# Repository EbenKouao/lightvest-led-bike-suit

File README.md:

# LightVest

LightVest is an open-source Bike Vest designed to be wearable technology. The product is a Bike Suit designed to increase a cyclist’s visibility, especially during the night. As well as improving cyclist communication and intent with other motorists and pedestrians.

## About this project:

This Bike Safety Product is designed to be open source. Feel free to contribute to make LightVest more robust. LightVest is designed for you to build on top of. Certain aspects of LightVest can be improved. Feel free to contribute, and explore more use cases.

Originally a video idea, aiming to build and launch a start-up in 4 weeks. You can find more information on the process on [smartbuilds.io](https://smartbuilds.io).
Alternatively, you can watch the full start up journey on my YouTube channel for context [Eben Kouao - The 4 Week Start-Up - Mini Documentary](https://www.youtube.com/channel/UCGxwyXJWEarxh2XWqvygiIg).

For more information visit: [lightvest.io](https://lightvest.io)

## Features

- A lightweight Weatherproof LED Vest (with IP67 Rated LEDs)
- Turn Signal’s – Fully programmable RGB LEDs
- Wireless remote to control the lights (with 4 fully customisable buttons)
- A Bike mount to attach to your Bike
- ON/OFF Switch Button
- Go Hand’s Free with an Inbuilt accelerometer – control Turn signals by from your bike handle
- Smart Mode – Send Data and track your Journey by Phone

## LightVest - Resources

This repo contains includes:

- Arduino Code
  - LightVest Remote
  - LightVest Wearable
- Breadboard Schematics (CAD and Fritzing)
  - LightVest Remote
  - LightVest Wearable
- PCB Schematics
  - LightVest Remote
  - LightVest Wearable
- 3D Prints
  - Remote
    - Breadboard Design:
      - Top Case
      - Bottom Case
      - Button (Arrow Keys)
    - PCB Design
      - Top Case
      - Bottom Case
      - Button (Circular)
  - Vest Case
  - L Connector Case

## Functionality of LightVest

| LED Strip            | Colour    | Function                |
| -------------------- | --------- | ----------------------- |
| Diamond Strip - Half | Yellow    | Turn Left or Right      |
| Diamond              | Strip Red | Red Abrupt Break Lights |
| Front Shoulder strip | Yellow    | Turn Left or Right      |
| All LED on Blinking  | Yellow    | Hazard / Emergency      |

## Requirement

Arduino Nano x 2
MPU6050 (Accelerometer)
LED Strip (WS2812B)
Jumper Wires
2 x Bluetooth HC-05

See the full Part List on LightVest's components on [smartbuilds.io](https://smartbuilds.io)

## Diagrams

### LightVest

### Remote

Support my [Future Projects on Patreon](https://www.patreon.com/ebenkouao)

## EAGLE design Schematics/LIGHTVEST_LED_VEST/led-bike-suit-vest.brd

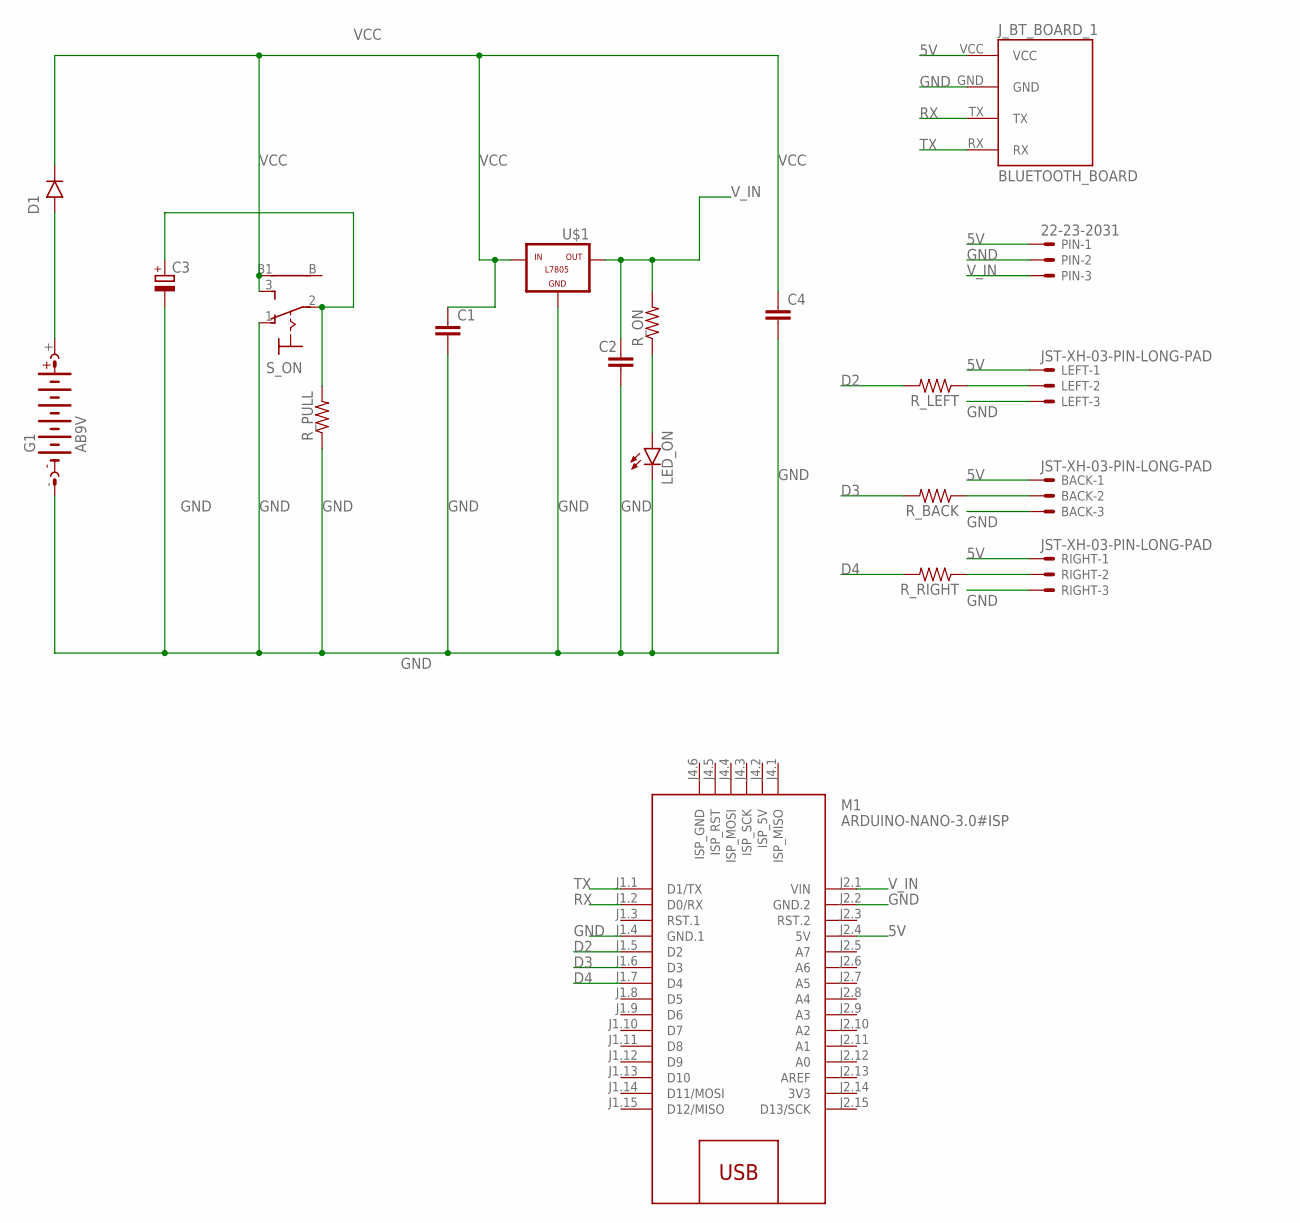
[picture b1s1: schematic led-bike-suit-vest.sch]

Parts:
BACK: JST-XH-03-PIN-LONG-PAD; JST-XH-03-PACKAGE-LONG-PAD
C1, C2, C4: C2.5/4; C2.5-4
C3: RCL_CPOL-EUE3.5-8; ELECTROLYTIC_CAP_RCL_E3,5-8
D1: 1N4001; DO41-10
G1: AB9V
J_BT_BOARD_1: BLUETOOTH_BOARD; BT_BOARD_FOOTPRINT
LED_ON: LED5MM
LEFT: JST-XH-03-PIN-LONG-PAD; JST-XH-03-PACKAGE-LONG-PAD
M1: ARDUINO-NANO-3.0#ISP
PIN: 22-23-2031
RIGHT: JST-XH-03-PIN-LONG-PAD; JST-XH-03-PACKAGE-LONG-PAD
R_BACK: PASSIVES_RESISTORPTH-1/4W; SPARKFUN-PASSIVES_AXIAL-0.4
R_LEFT: PASSIVES_RESISTORPTH-1/4W; SPARKFUN-PASSIVES_AXIAL-0.4
R_ON: PASSIVES_RESISTORPTH-1/4W; SPARKFUN-PASSIVES_AXIAL-0.4
R_PULL: PASSIVES_RESISTORPTH-1/4W; SPARKFUN-PASSIVES_AXIAL-0.4
R_RIGHT: PASSIVES_RESISTORPTH-1/4W; SPARKFUN-PASSIVES_AXIAL-0.4
S_ON: 9070-1W
U$1: -L7805; L7805

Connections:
3V3: M1.J2.14 (3V3)
5V: BACK.1, J_BT_BOARD_1.VCC, LEFT.1, M1.J2.4 (5V), PIN.1, RIGHT.1
D2: M1.J1.5 (D2), R_LEFT.P$2 (2)
D3: M1.J1.6 (D3), R_BACK.P$2 (2)
D4: M1.J1.7 (D4), R_RIGHT.P$2 (2)
GND: BACK.3, C1.2, C2.2, C3.-, C4.2, G1.-, J_BT_BOARD_1.GND, LED_ON.K (CATHODE), LEFT.3, M1.J1.4 (GND.1), M1.J2.2 (GND.2), PIN.2, RIGHT.3, R_PULL.P$1 (1), S_ON.1 (O), U$1.GND
unnamed: BACK.2, R_BACK.P$1 (1)
unnamed: LEFT.2, R_LEFT.P$1 (1)
unnamed: RIGHT.2, R_RIGHT.P$1 (1)
unnamed: C3.+, R_PULL.P$2 (2), S_ON.2
unnamed: D1.A (ANODE), G1.+
unnamed: LED_ON.A (ANODE), R_ON.P$1 (1)
RX: J_BT_BOARD_1.TX, M1.J1.2 (D0/RX)
TX: J_BT_BOARD_1.RX, M1.J1.1 (D1/TX)
VCC: C1.1, C4.1, D1.C (CATHODE), S_ON.3 (S), S_ON.B1, U$1.IN
V_IN: C2.1, M1.J2.1 (VIN), PIN.3, R_ON.P$2 (2), U$1.OUT

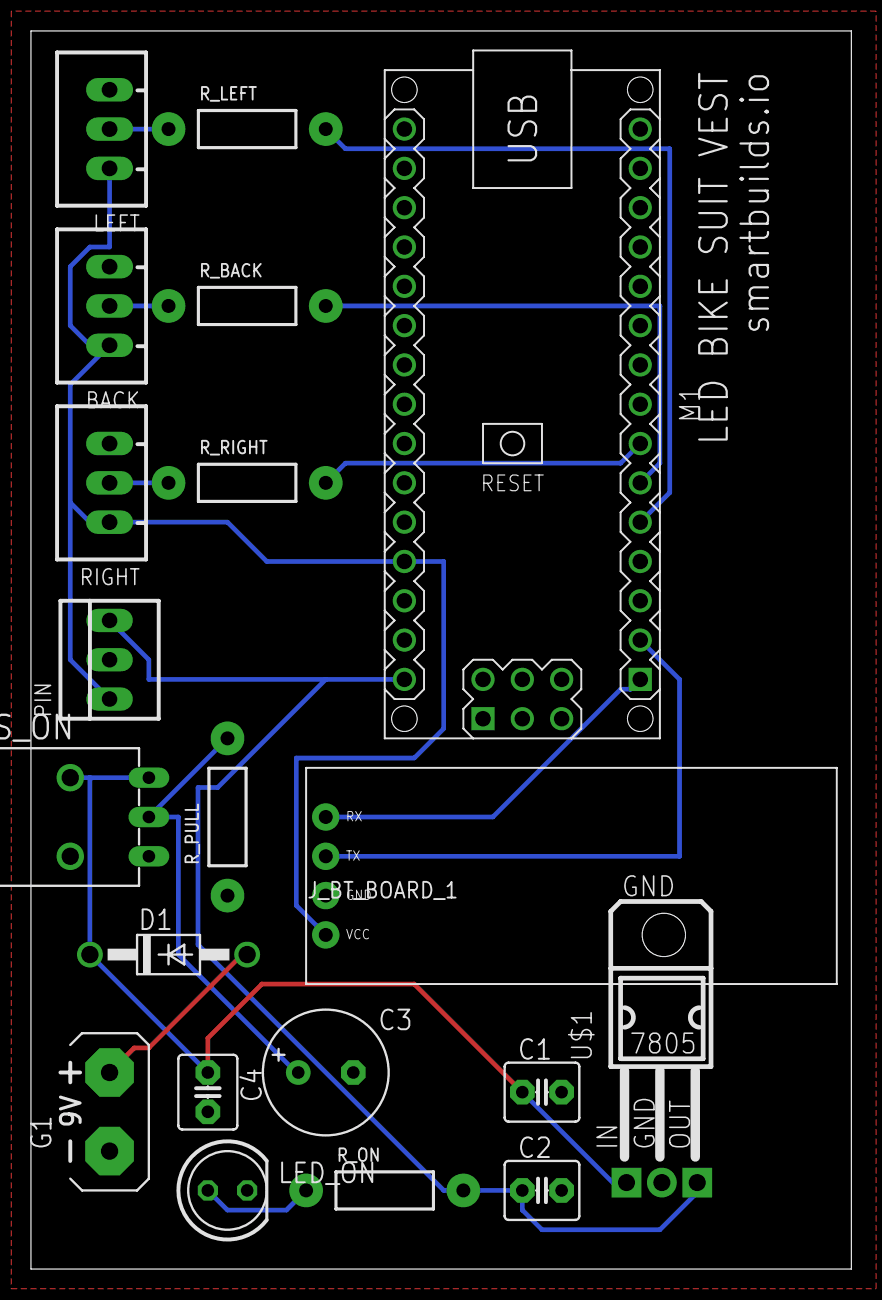
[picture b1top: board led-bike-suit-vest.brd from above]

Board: 2 copper layers, 53.0 x 80.0 mm, 20 parts (0 on the bottom side), 15 nets.

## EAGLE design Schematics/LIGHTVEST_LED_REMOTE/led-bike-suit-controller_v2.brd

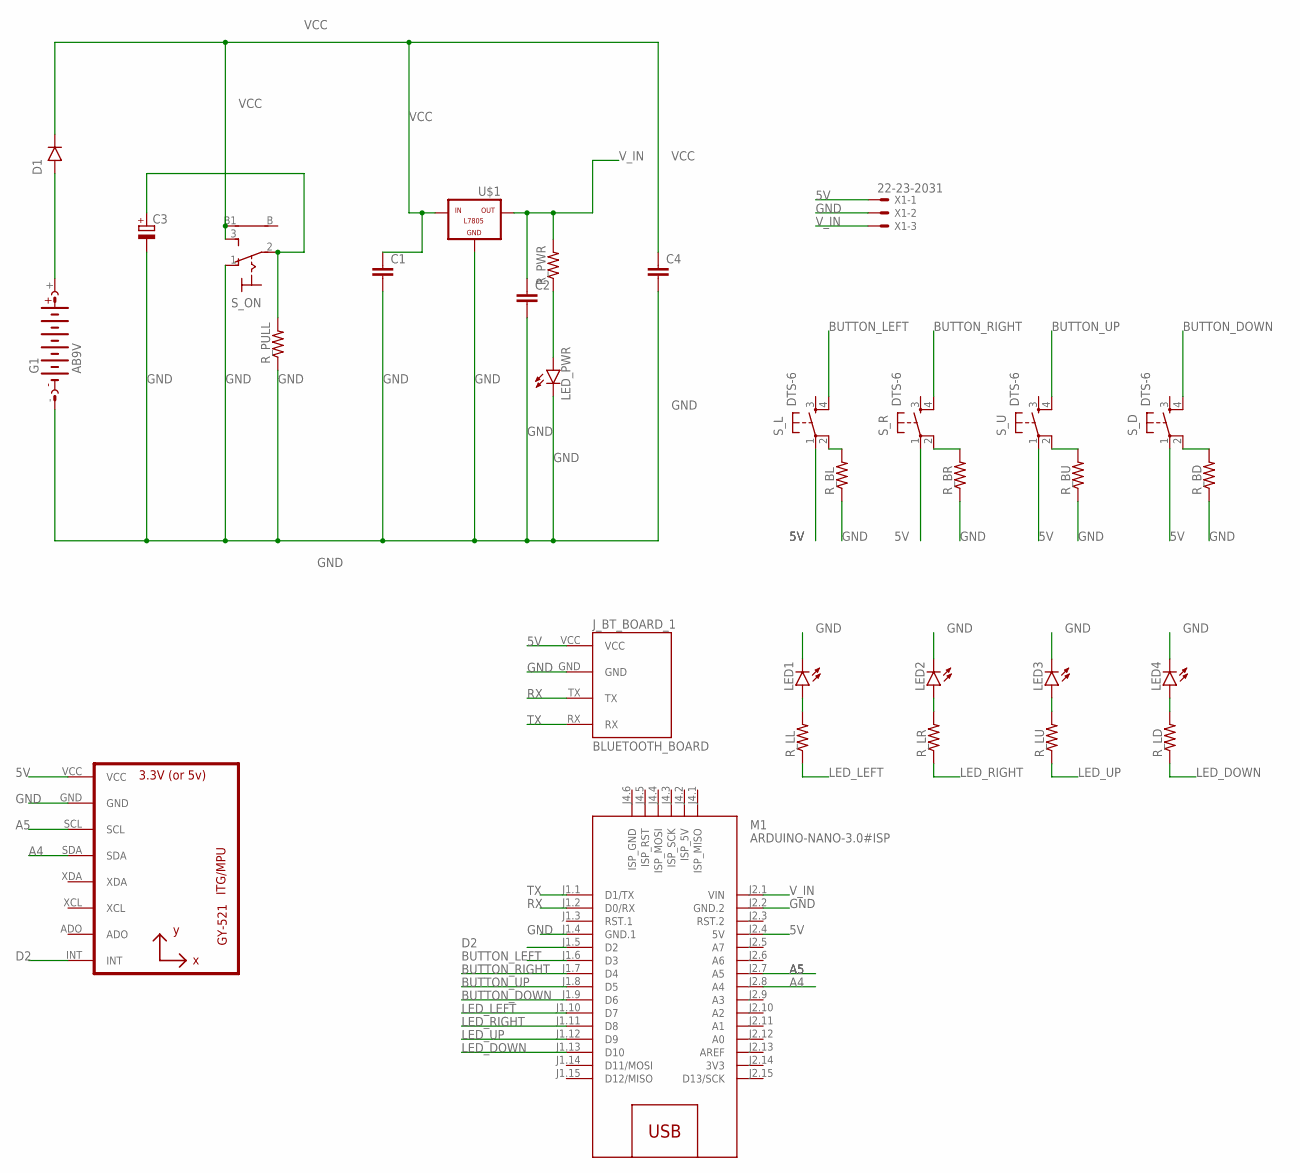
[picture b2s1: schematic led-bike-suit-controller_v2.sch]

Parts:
C1, C2, C4: C2.5/4; C2.5-4
C3: RCL_CPOL-EUE3.5-8; ELECTROLYTIC_CAP_RCL_E3,5-8
D1: 1N4001; DO41-10
G1: AB9V
J_BT_BOARD_1: BLUETOOTH_BOARD; BT_BOARD_FOOTPRINT
LED1, LED2, LED3, LED4: LED5MM; SPARKFUN-LED_LED5MM
LED_PWR: LED5MM
M1: ARDUINO-NANO-3.0#ISP
R_BD: PASSIVES_RESISTORPTH-1/4W; SPARKFUN-PASSIVES_AXIAL-0.4
R_BL: PASSIVES_RESISTORPTH-1/4W; SPARKFUN-PASSIVES_AXIAL-0.4
R_BR: PASSIVES_RESISTORPTH-1/4W; SPARKFUN-PASSIVES_AXIAL-0.4
R_BU: PASSIVES_RESISTORPTH-1/4W; SPARKFUN-PASSIVES_AXIAL-0.4
R_LD: PASSIVES_RESISTORPTH-1/4W; SPARKFUN-PASSIVES_AXIAL-0.4
R_LL: PASSIVES_RESISTORPTH-1/4W; SPARKFUN-PASSIVES_AXIAL-0.4
R_LR: PASSIVES_RESISTORPTH-1/4W; SPARKFUN-PASSIVES_AXIAL-0.4
R_LU: PASSIVES_RESISTORPTH-1/4W; SPARKFUN-PASSIVES_AXIAL-0.4
R_PULL: PASSIVES_RESISTORPTH-1/4W; SPARKFUN-PASSIVES_AXIAL-0.4
R_PWR: PASSIVES_RESISTORPTH-1/4W; SPARKFUN-PASSIVES_AXIAL-0.4
S_D: DTS-6
S_L: DTS-6
S_ON: 9070-1W
S_R: DTS-6
S_U: DTS-6
U1: GY-521MPU6050; GY-521
U$1: -L7805; L7805
X1: 22-23-2031

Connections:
3V3: M1.J2.14 (3V3)
5V: J_BT_BOARD_1.VCC, M1.J2.4 (5V), S_D.1, S_L.1, S_R.1, S_U.1, U1.VCC, X1.1
A4: M1.J2.8 (A4), U1.SDA
A5: M1.J2.7 (A5), U1.SCL
BUTTON_DOWN: M1.J1.9 (D6), S_D.4
BUTTON_LEFT: M1.J1.6 (D3), S_L.4
BUTTON_RIGHT: M1.J1.7 (D4), S_R.4
BUTTON_UP: M1.J1.8 (D5), S_U.4
D2: M1.J1.5 (D2), U1.INT
GND: C1.2, C2.2, C3.-, C4.2, G1.-, J_BT_BOARD_1.GND, LED1.K (C), LED2.K (C), LED3.K (C), LED4.K (C), LED_PWR.K (CATHODE), M1.J1.4 (GND.1), M1.J2.2 (GND.2), R_BD.P$1 (1), R_BL.P$1 (1), R_BR.P$1 (1), R_BU.P$1 (1), R_PULL.P$1 (1), S_ON.1 (O), U1.GND, U$1.GND, X1.2
LED_DOWN: M1.J1.13 (D10), R_LD.P$1 (1)
LED_LEFT: M1.J1.10 (D7), R_LL.P$1 (1)
LED_RIGHT: M1.J1.11 (D8), R_LR.P$1 (1)
LED_UP: M1.J1.12 (D9), R_LU.P$1 (1)
unnamed: LED1.A, R_LL.P$2 (2)
unnamed: R_BU.P$2 (2), S_U.2
unnamed: R_BD.P$2 (2), S_D.2
unnamed: LED2.A, R_LR.P$2 (2)
unnamed: R_BL.P$2 (2), S_L.2
unnamed: R_BR.P$2 (2), S_R.2
unnamed: LED3.A, R_LU.P$2 (2)
unnamed: LED4.A, R_LD.P$2 (2)
unnamed: C3.+, R_PULL.P$2 (2), S_ON.2
unnamed: D1.A (ANODE), G1.+
unnamed: LED_PWR.A (ANODE), R_PWR.P$1 (1)
RX: J_BT_BOARD_1.TX, M1.J1.2 (D0/RX)
TX: J_BT_BOARD_1.RX, M1.J1.1 (D1/TX)
VCC: C1.1, C4.1, D1.C (CATHODE), S_ON.3 (S), S_ON.B1, U$1.IN
V_IN: C2.1, M1.J2.1 (VIN), R_PWR.P$2 (2), U$1.OUT, X1.3

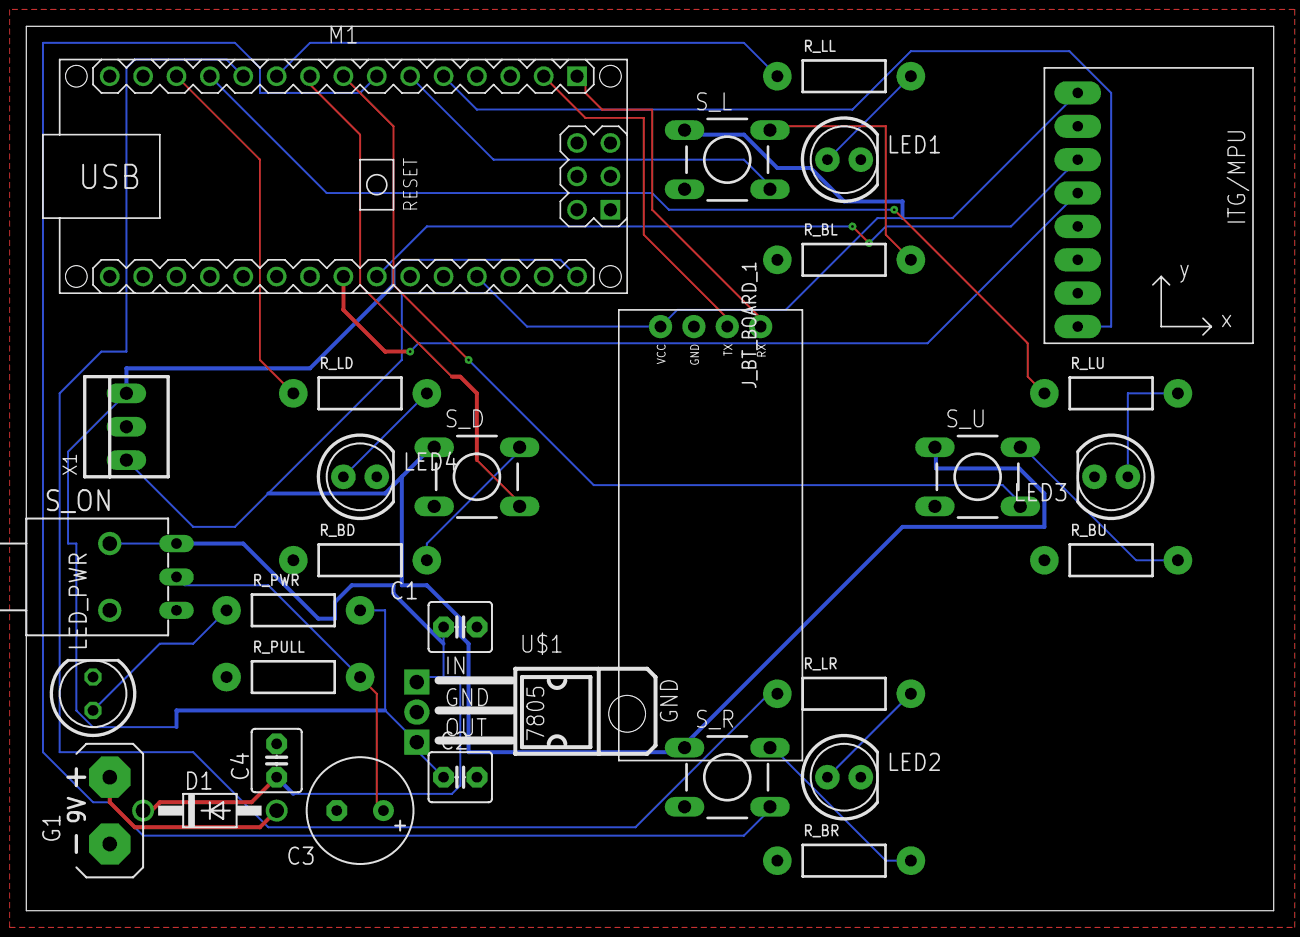
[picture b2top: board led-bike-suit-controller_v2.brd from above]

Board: 2 copper layers, 94.9 x 67.3 mm, 31 parts (0 on the bottom side), 28 nets.

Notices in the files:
parts and their libraries:
diy-modules: Released under the Creative Commons Attribution 4.0 International License: http://creativecommons.org/licenses/by/4.0
